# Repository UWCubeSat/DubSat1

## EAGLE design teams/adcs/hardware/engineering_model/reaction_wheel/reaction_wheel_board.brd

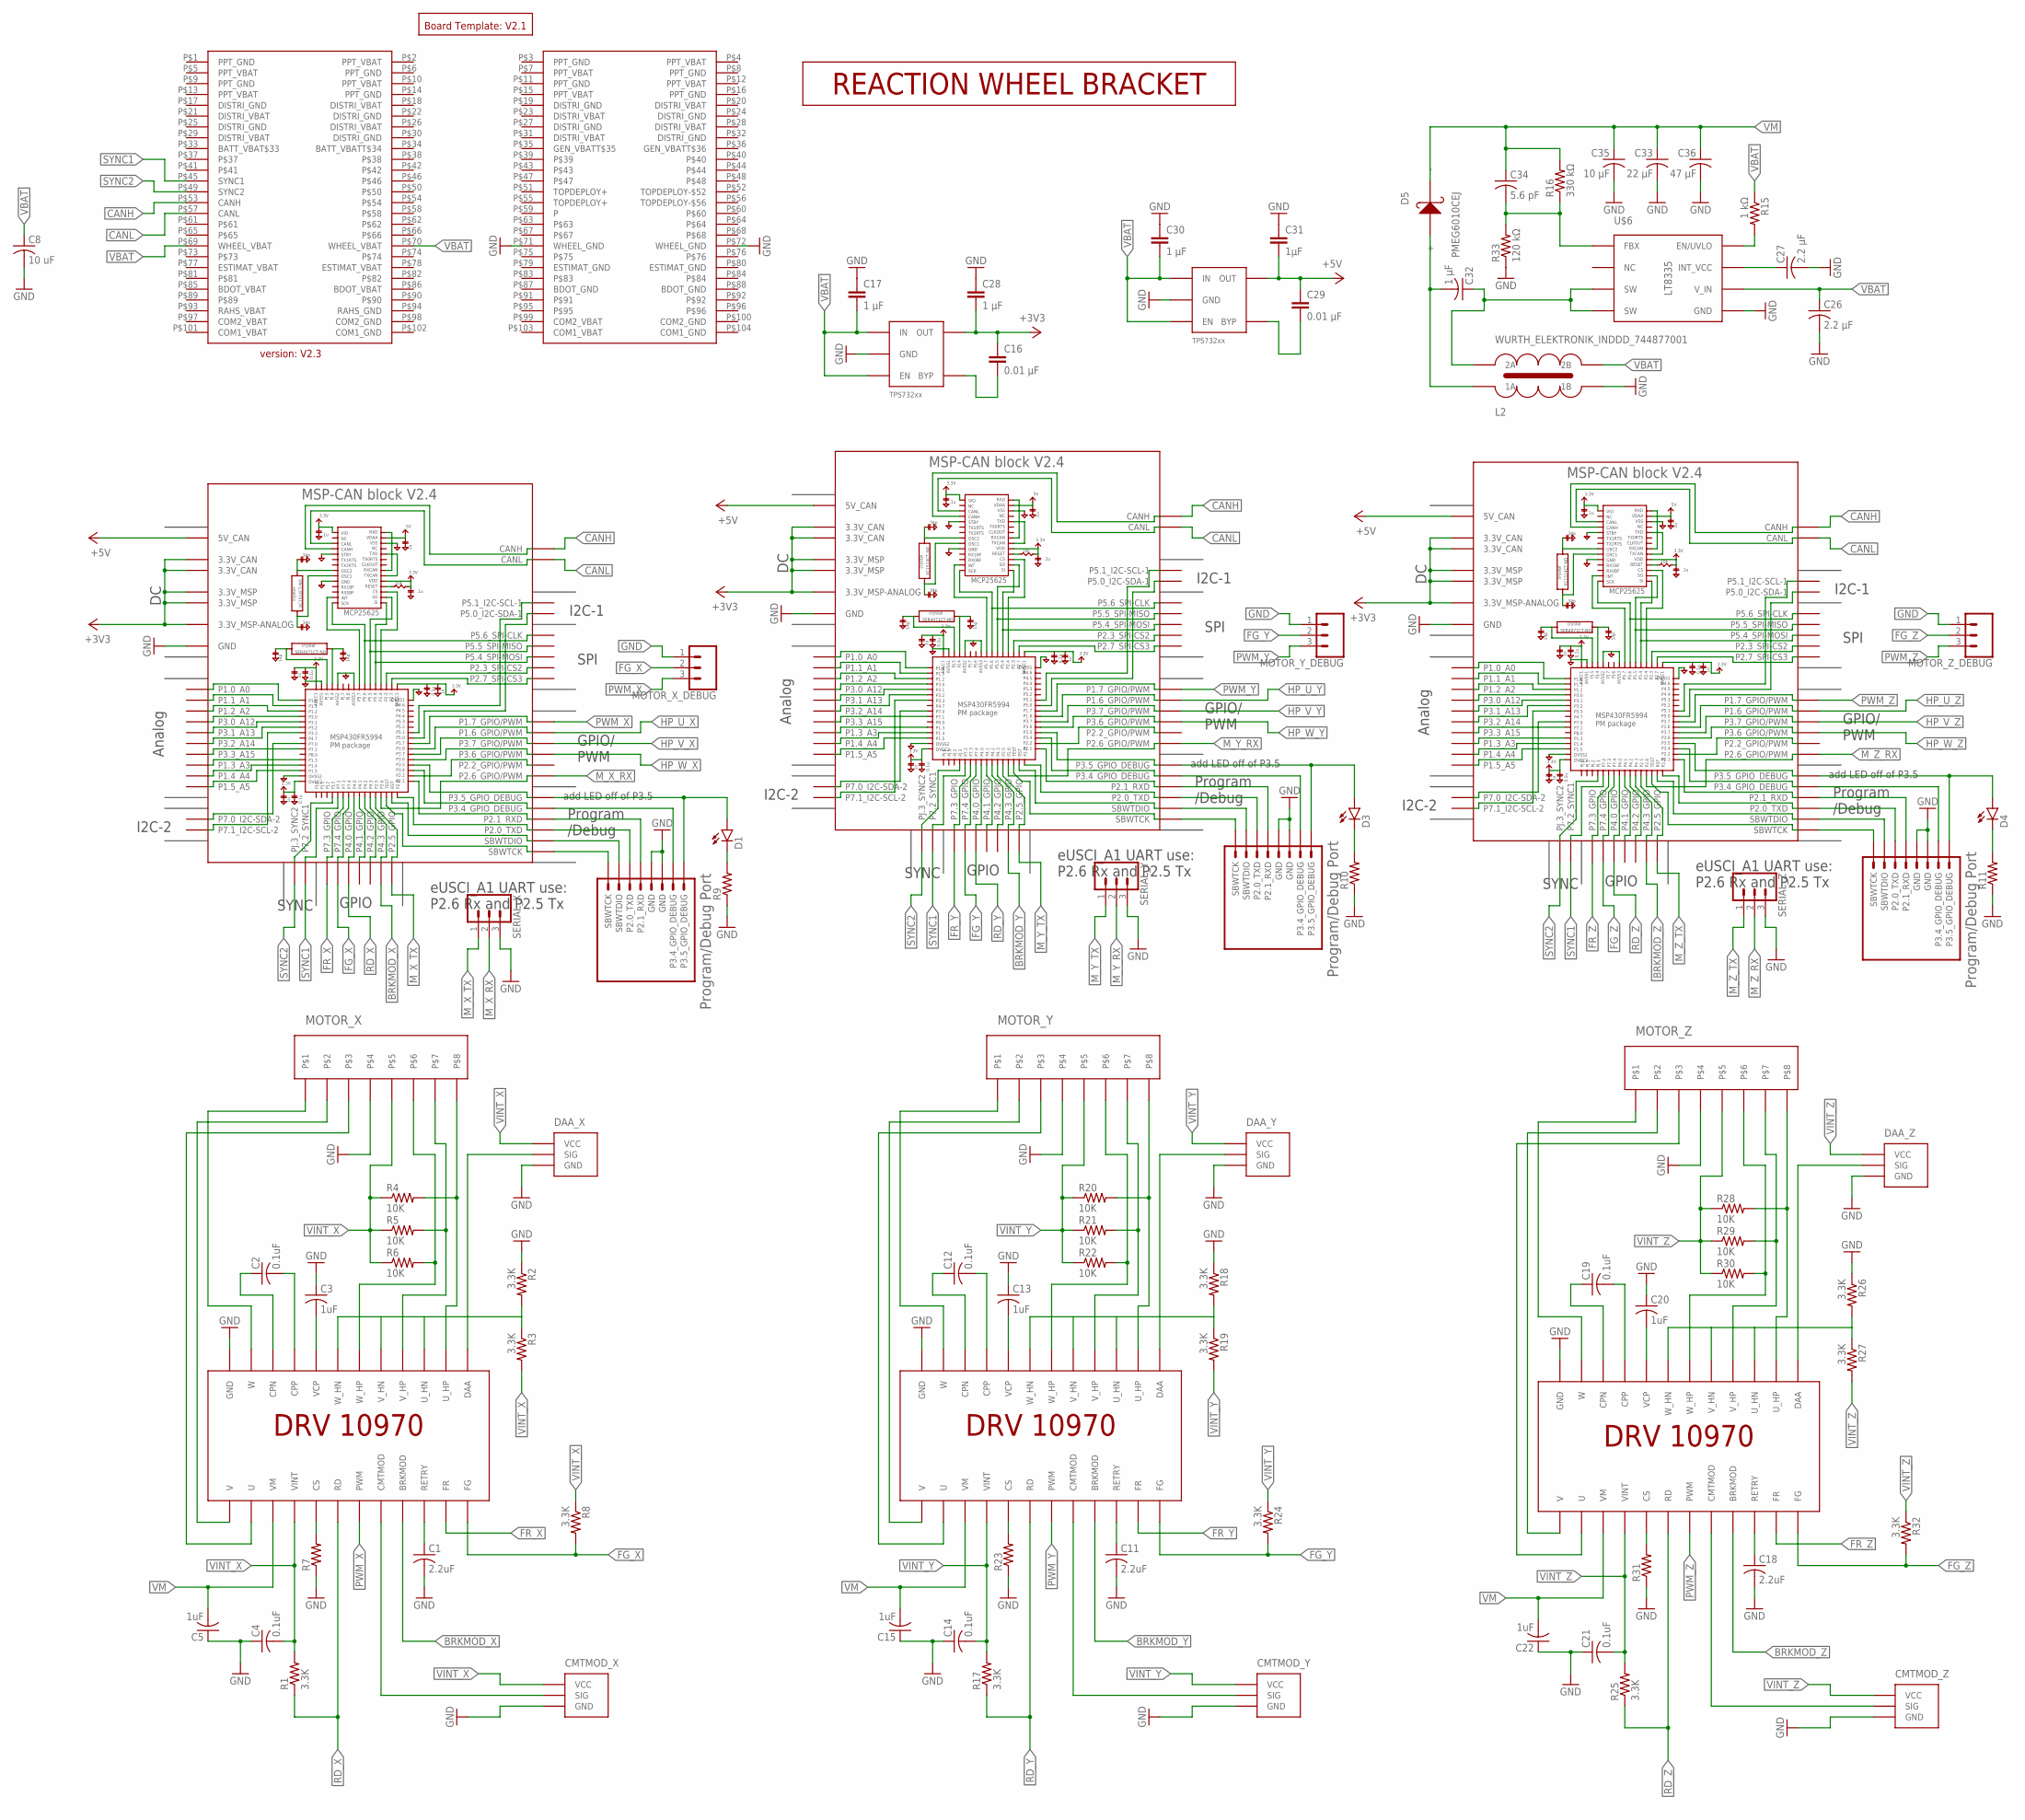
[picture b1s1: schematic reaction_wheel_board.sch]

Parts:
C1, C11, C18: 2.2uF; C1206
C2, C4, C12, C14, C19, C21: 0.1uF; C0805
C3, C5, C13, C15, C20, C22: 1uF; C1206
C8: 10 uF; C0805
C16, C29: 0.01 μF; 0805
C17, C28, C30: 1 μF; 0805
C26, C27: 2.2 μF; C0805
C31: 1μF; 0805
C32: 1 μF; C0805
C33: 22 μF; C1206
C34: 5.6 pF; C0805
C35: 10 μF; C0805
C36: 47 μF; C1206
CMTMOD_X: 0_OHM_JUMPER
CMTMOD_Y: 0_OHM_JUMPER
CMTMOD_Z: 0_OHM_JUMPER
D1, D3, D4: LED; LED-1206
D5: PMEG6010CEJ; SC-90
DAA_X: 0_OHM_JUMPER
DAA_Y: 0_OHM_JUMPER
DAA_Z: 0_OHM_JUMPER
L2: WURTH_ELEKTRONIK_INDDD_744877001
MOTOR_X: PICOLOCK_8
MOTOR_X_DEBUG: CONN_03LOCK; 1X03_LOCK
MOTOR_Y: PICOLOCK_8
MOTOR_Y_DEBUG: CONN_03LOCK; 1X03_LOCK
MOTOR_Z: PICOLOCK_8
MOTOR_Z_DEBUG: CONN_03LOCK; 1X03_LOCK
MSP_X_DEBUG: PROGRAM/DEBUG_PORT; 1X08_CONNECTOR
MSP_Y_DEBUG: PROGRAM/DEBUG_PORT; 1X08_CONNECTOR
MSP_Z_DEBUG: PROGRAM/DEBUG_PORT; 1X08_CONNECTOR
PC104: PC104_CONNECTOR
R1, R2, R3, R8, R17, R18, R19, R24, R25, R26, R27, R32: 3.3K; 0805
R4, R5, R6, R20, R21, R22, R28, R29, R30: 10K; 0805
R7, R9, R10, R11, R23, R31: RESISTOR0805; 0805
R15: 1 kΩ; 0805
R16: 330 kΩ; 0805
R33: 120 kΩ; 0805
SERIAL_X: CONN_03LOCK; 1X03_LOCK
SERIAL_Y: CONN_03LOCK; 1X03_LOCK
SERIAL_Z: CONN_03LOCK; 1X03_LOCK
U2, U3: TPS732XX; SOT-23-5
U$1: BOARD_TEMPLATESERCURED; BOARD_TEMPLATE_SECURED
U$3, U$10, U$13: MSP-CAN_BLOCK
U$6: LT8335; DDB
U$7, U$12, U$15: DRV10970
U$9: REACTION_WHEEL_BRACKET

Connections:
+3V3: C16.1, C28.2, U2.P$5 (OUT), U$3.3.3V@CAN1 (3.3V_CAN), U$3.3.3V@CAN2 (3.3V_CAN), U$3.3.3V@MSP1 (3.3V_MSP), U$3.3.3V@MSP2 (3.3V_MSP), U$3.3.3V_ANALOG@MSP2 (3.3V_MSP-ANALOG), U$10.3.3V@CAN1 (3.3V_CAN), U$10.3.3V@CAN2 (3.3V_CAN), U$10.3.3V@MSP1 (3.3V_MSP), U$10.3.3V@MSP2 (3.3V_MSP), U$10.3.3V_ANALOG@MSP2 (3.3V_MSP-ANALOG), U$13.3.3V@CAN1 (3.3V_CAN), U$13.3.3V@CAN2 (3.3V_CAN), U$13.3.3V@MSP1 (3.3V_MSP), U$13.3.3V@MSP2 (3.3V_MSP), U$13.3.3V_ANALOG@MSP2 (3.3V_MSP-ANALOG)
+5V: C29.1, C31.2, U3.P$5 (OUT), U$3.5V (5V_CAN), U$10.5V (5V_CAN), U$13.5V (5V_CAN)
BRKMOD_X: U$3.P4.3_GPIO, U$7.BRKMOD
BRKMOD_Y: U$10.P4.3_GPIO, U$12.BRKMOD
BRKMOD_Z: U$13.P4.3_GPIO, U$15.BRKMOD
CANH: PC104.P$53 (CANH), U$3.CANH, U$10.CANH, U$13.CANH
CANL: PC104.P$57 (CANL), U$3.CANL, U$10.CANL, U$13.CANL
CMTMOD_X: CMTMOD_X.P$2 (SIG), U$7.CMTMOD
CMTMOD_Y: CMTMOD_Y.P$2 (SIG), U$12.CMTMOD
CMTMOD_Z: CMTMOD_Z.P$2 (SIG), U$15.CMTMOD
CPN_X: C2.1, U$7.CPN
CPN_Y: C12.1, U$12.CPN
CPN_Z: C19.1, U$15.CPN
CPP_X: C2.2, U$7.CPP
CPP_Y: C12.2, U$12.CPP
CPP_Z: C19.2, U$15.CPP
CS_X: R7.2, U$7.CS
CS_Y: R23.2, U$12.CS
CS_Z: R31.2, U$15.CS
DAA_X: DAA_X.P$2 (SIG), U$7.DAA
DAA_Y: DAA_Y.P$2 (SIG), U$12.DAA
DAA_Z: DAA_Z.P$2 (SIG), U$15.DAA
EN_UVLO: R15.2, U$6.P$8 (EN/UVLO)
FBX: C34.2, R16.1, R33.2, U$6.P$1 (FBX)
FG_X: MOTOR_X_DEBUG.2, R8.2, U$3.P7.4_GPIO, U$7.FG
FG_Y: MOTOR_Y_DEBUG.2, R24.2, U$10.P7.4_GPIO, U$12.FG
FG_Z: MOTOR_Z_DEBUG.2, R32.2, U$13.P7.4_GPIO, U$15.FG
FR_X: U$3.P7.3_GPIO, U$7.FR
FR_Y: U$10.P7.3_GPIO, U$12.FR
FR_Z: U$13.P7.3_GPIO, U$15.FR
GND: C1.2, C3.1, C4.1, C5.1, C8.2, C11.2, C13.1, C14.1, C15.1, C17.1, C18.2, C20.1, C21.1, C22.1, C26.2, C27.2, C28.1, C30.1, C31.1, C33.2, C35.2, C36.2, CMTMOD_X.P$1 (GND), CMTMOD_Y.P$1 (GND), CMTMOD_Z.P$1 (GND), DAA_X.P$1 (GND), DAA_Y.P$1 (GND), DAA_Z.P$1 (GND), L2.P$2 (1B), MOTOR_X.P$4, MOTOR_X_DEBUG.1, MOTOR_Y.P$4, MOTOR_Y_DEBUG.1, MOTOR_Z.P$4, MOTOR_Z_DEBUG.1, MSP_X_DEBUG.5 (GND), MSP_X_DEBUG.6 (GND), MSP_Y_DEBUG.5 (GND), MSP_Y_DEBUG.6 (GND), MSP_Z_DEBUG.5 (GND), MSP_Z_DEBUG.6 (GND), PC104.P$71 (WHEEL_GND), PC104.P$72 (WHEEL_GND), R2.1, R7.1, R9.1, R10.1, R11.1, R18.1, R23.1, R26.1, R31.1, R33.1, SERIAL_X.3, SERIAL_Y.3, SERIAL_Z.3, U2.P$2 (GND), U3.P$2 (GND), U$3.GND@1 (GND), U$3.GND@2 (GND), U$3.GND@3 (GND), U$3.GND@4 (GND), U$3.GND@5 (GND), U$3.GND@7 (GND), U$3.GND@8 (GND), U$3.GND@9 (GND), U$3.GND@10 (GND), U$3.GND@11 (GND), U$3.GND@12 (GND), U$3.GND@13 (GND), U$3.GND@14 (GND), U$3.GND@15 (GND), U$3.GND@16 (GND), U$3.GND@17 (GND), U$3.GND@26 (GND), U$6.GND, U$6.P$5 (GND), U$7.GND@1 (GND), U$7.GND@2 (GND), U$10.GND@1 (GND), U$10.GND@2 (GND), U$10.GND@3 (GND), U$10.GND@4 (GND), U$10.GND@5 (GND), U$10.GND@7 (GND), U$10.GND@8 (GND), U$10.GND@9 (GND), U$10.GND@10 (GND), U$10.GND@11 (GND), U$10.GND@12 (GND), U$10.GND@13 (GND), U$10.GND@14 (GND), U$10.GND@15 (GND), U$10.GND@16 (GND), U$10.GND@17 (GND), U$10.GND@26 (GND), U$12.GND@1 (GND), U$12.GND@2 (GND), U$13.GND@1 (GND), U$13.GND@2 (GND), U$13.GND@3 (GND), U$13.GND@4 (GND), U$13.GND@5 (GND), U$13.GND@7 (GND), U$13.GND@8 (GND), U$13.GND@9 (GND), U$13.GND@10 (GND), U$13.GND@11 (GND), U$13.GND@12 (GND), U$13.GND@13 (GND), U$13.GND@14 (GND), U$13.GND@15 (GND), U$13.GND@16 (GND), U$13.GND@17 (GND), U$13.GND@26 (GND), U$15.GND@1 (GND), U$15.GND@2 (GND)
GPIO_DEBUG_3.4_X: MSP_X_DEBUG.7 (P3.4_GPIO_DEBUG), U$3.P3.4_GPIO_DEBUG
GPIO_DEBUG_3.4_Y: MSP_Y_DEBUG.7 (P3.4_GPIO_DEBUG), U$10.P3.4_GPIO_DEBUG
GPIO_DEBUG_3.4_Z: MSP_Z_DEBUG.7 (P3.4_GPIO_DEBUG), U$13.P3.4_GPIO_DEBUG
GPIO_DEBUG_3.5_X: D1.A, MSP_X_DEBUG.8 (P3.5_GPIO_DEBUG), U$3.P3.5_GPIO_DEBUG
GPIO_DEBUG_3.5_Y: D3.A, MSP_Y_DEBUG.8 (P3.5_GPIO_DEBUG), U$10.P3.5_GPIO_DEBUG
GPIO_DEBUG_3.5_Z: D4.A, MSP_Z_DEBUG.8 (P3.5_GPIO_DEBUG), U$13.P3.5_GPIO_DEBUG
HN_X: R2.2, R3.1, U$7.U_HN, U$7.V_HN, U$7.W_HN
HN_Y: R18.2, R19.1, U$12.U_HN, U$12.V_HN, U$12.W_HN
HN_Z: R26.2, R27.1, U$15.U_HN, U$15.V_HN, U$15.W_HN
HP_U_X: MOTOR_X.P$8, R4.2, U$3.P1.6_GPIO/PWM, U$7.U_HP
HP_U_Y: MOTOR_Y.P$8, R20.2, U$10.P1.6_GPIO/PWM, U$12.U_HP
HP_U_Z: MOTOR_Z.P$8, R28.2, U$13.P1.6_GPIO/PWM, U$15.U_HP
HP_V_X: MOTOR_X.P$7, R5.2, U$3.P3.7_GPIO/PWM, U$7.V_HP
HP_V_Y: MOTOR_Y.P$7, R21.2, U$10.P3.7_GPIO/PWM, U$12.V_HP
HP_V_Z: MOTOR_Z.P$7, R29.2, U$13.P3.7_GPIO/PWM, U$15.V_HP
HP_W_X: MOTOR_X.P$6, R6.2, U$3.P3.6_GPIO/PWM, U$7.W_HP
HP_W_Y: MOTOR_Y.P$6, R22.2, U$10.P3.6_GPIO/PWM, U$12.W_HP
HP_W_Z: MOTOR_Z.P$6, R30.2, U$13.P3.6_GPIO/PWM, U$15.W_HP
INT_VCC: C27.1, U$6.P$7 (INT_VCC)
LDO_3V3_BYP2: C16.2, U2.P$4 (BYP)
LDO_5V_BYP: C29.2, U3.P$4 (BYP)
M_X_RX: SERIAL_X.2, U$3.P2.6_GPIO/PWM
M_X_TX: SERIAL_X.1, U$3.P2.5_GPIO
M_Y_RX: SERIAL_Y.2, U$10.P2.6_GPIO/PWM
M_Y_TX: SERIAL_Y.1, U$10.P2.5_GPIO
M_Z_RX: SERIAL_Z.2, U$13.P2.6_GPIO/PWM
M_Z_TX: SERIAL_Z.1, U$13.P2.5_GPIO
unnamed: D4.C, R11.2
unnamed: D3.C, R10.2
unnamed: D1.C, R9.2
PWM_X: MOTOR_X_DEBUG.3, U$3.P1.7_GPIO/PWM, U$7.PWM
PWM_Y: MOTOR_Y_DEBUG.3, U$10.P1.7_GPIO/PWM, U$12.PWM
PWM_Z: MOTOR_Z_DEBUG.3, U$13.P1.7_GPIO/PWM, U$15.PWM
RD_X: R1.1, U$3.P4.0_GPIO, U$7.RD
RD_Y: R17.1, U$10.P4.0_GPIO, U$12.RD
RD_Z: R25.1, U$13.P4.0_GPIO, U$15.RD
RETRY_X: C1.1, U$7.RETRY
RETRY_Y: C11.1, U$12.RETRY
RETRY_Z: C18.1, U$15.RETRY
RXD_X: MSP_X_DEBUG.4 (P2.1_RXD), U$3.P2.1_RXD
RXD_Y: MSP_Y_DEBUG.4 (P2.1_RXD), U$10.P2.1_RXD
RXD_Z: MSP_Z_DEBUG.4 (P2.1_RXD), U$13.P2.1_RXD
SBWTCK_X: MSP_X_DEBUG.SBWTCK, U$3.SBWTCK
SBWTCK_Y: MSP_Y_DEBUG.SBWTCK, U$10.SBWTCK
SBWTCK_Z: MSP_Z_DEBUG.SBWTCK, U$13.SBWTCK
SBWTDIO_X: MSP_X_DEBUG.2 (SBWTDIO), U$3.SBWTDIO
SBWTDIO_Y: MSP_Y_DEBUG.2 (SBWTDIO), U$10.SBWTDIO
SBWTDIO_Z: MSP_Z_DEBUG.2 (SBWTDIO), U$13.SBWTDIO
SW: C32.1, L2.P$3 (2A), U$6.P$3 (SW), U$6.P$4 (SW)
SYNC1: PC104.P$45 (SYNC1), U$3.P7.2_SYNC1, U$10.P7.2_SYNC1, U$13.P7.2_SYNC1
SYNC2: PC104.P$49 (SYNC2), U$3.PJ.3_SYNC2, U$10.PJ.3_SYNC2, U$13.PJ.3_SYNC2
TXD_X: MSP_X_DEBUG.3 (P2.0_TXD), U$3.P2.0_TXD
TXD_Y: MSP_Y_DEBUG.3 (P2.0_TXD), U$10.P2.0_TXD
TXD_Z: MSP_Z_DEBUG.3 (P2.0_TXD), U$13.P2.0_TXD
U_X: MOTOR_X.P$3, U$7.U
U_Y: MOTOR_Y.P$3, U$12.U
U_Z: MOTOR_Z.P$3, U$15.U
VBAT: C8.1, C17.2, C26.1, C30.2, L2.P$4 (2B), PC104.P$69 (WHEEL_VBAT), PC104.P$70 (WHEEL_VBAT), R15.1, U2.P$1 (IN), U2.P$3 (EN), U3.P$1 (IN), U3.P$3 (EN), U$6.P$6 (V_IN)
VCP_X: C3.2, U$7.VCP
VCP_Y: C13.2, U$12.VCP
VCP_Z: C20.2, U$15.VCP
VD: C32.2, D5.P$1 (+), L2.P$1 (1A)
VINT_X: C4.2, CMTMOD_X.P$3 (VCC), DAA_X.P$3 (VCC), MOTOR_X.P$5, R1.2, R3.2, R4.1, R5.1, R6.1, R8.1, U$7.VINT
VINT_Y: C14.2, CMTMOD_Y.P$3 (VCC), DAA_Y.P$3 (VCC), MOTOR_Y.P$5, R17.2, R19.2, R20.1, R21.1, R22.1, R24.1, U$12.VINT
VINT_Z: C21.2, CMTMOD_Z.P$3 (VCC), DAA_Z.P$3 (VCC), MOTOR_Z.P$5, R25.2, R27.2, R28.1, R29.1, R30.1, R32.1, U$15.VINT
VM: C5.2, C15.2, C22.2, C33.1, C34.1, C35.1, C36.1, D5.P$2 (-), R16.2, U$7.VM, U$12.VM, U$15.VM
V_X: MOTOR_X.P$2, U$7.V
V_Y: MOTOR_Y.P$2, U$12.V
V_Z: MOTOR_Z.P$2, U$15.V
W_X: MOTOR_X.P$1, U$7.W
W_Y: MOTOR_Y.P$1, U$12.W
W_Z: MOTOR_Z.P$1, U$15.W

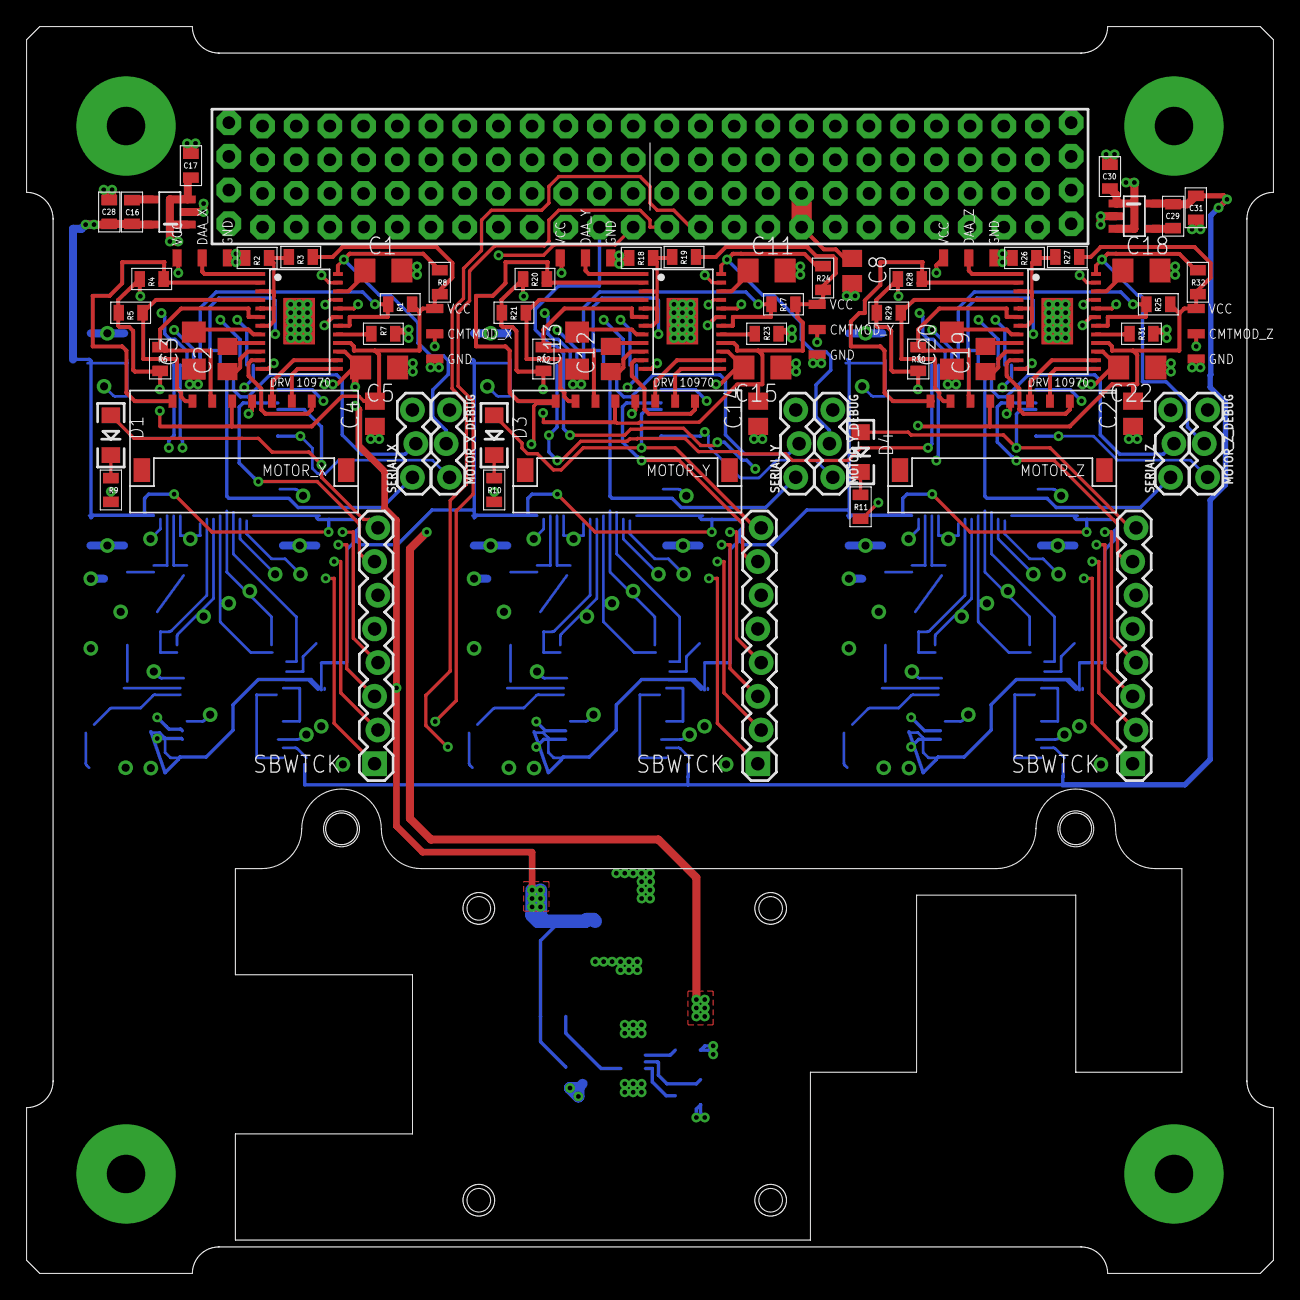
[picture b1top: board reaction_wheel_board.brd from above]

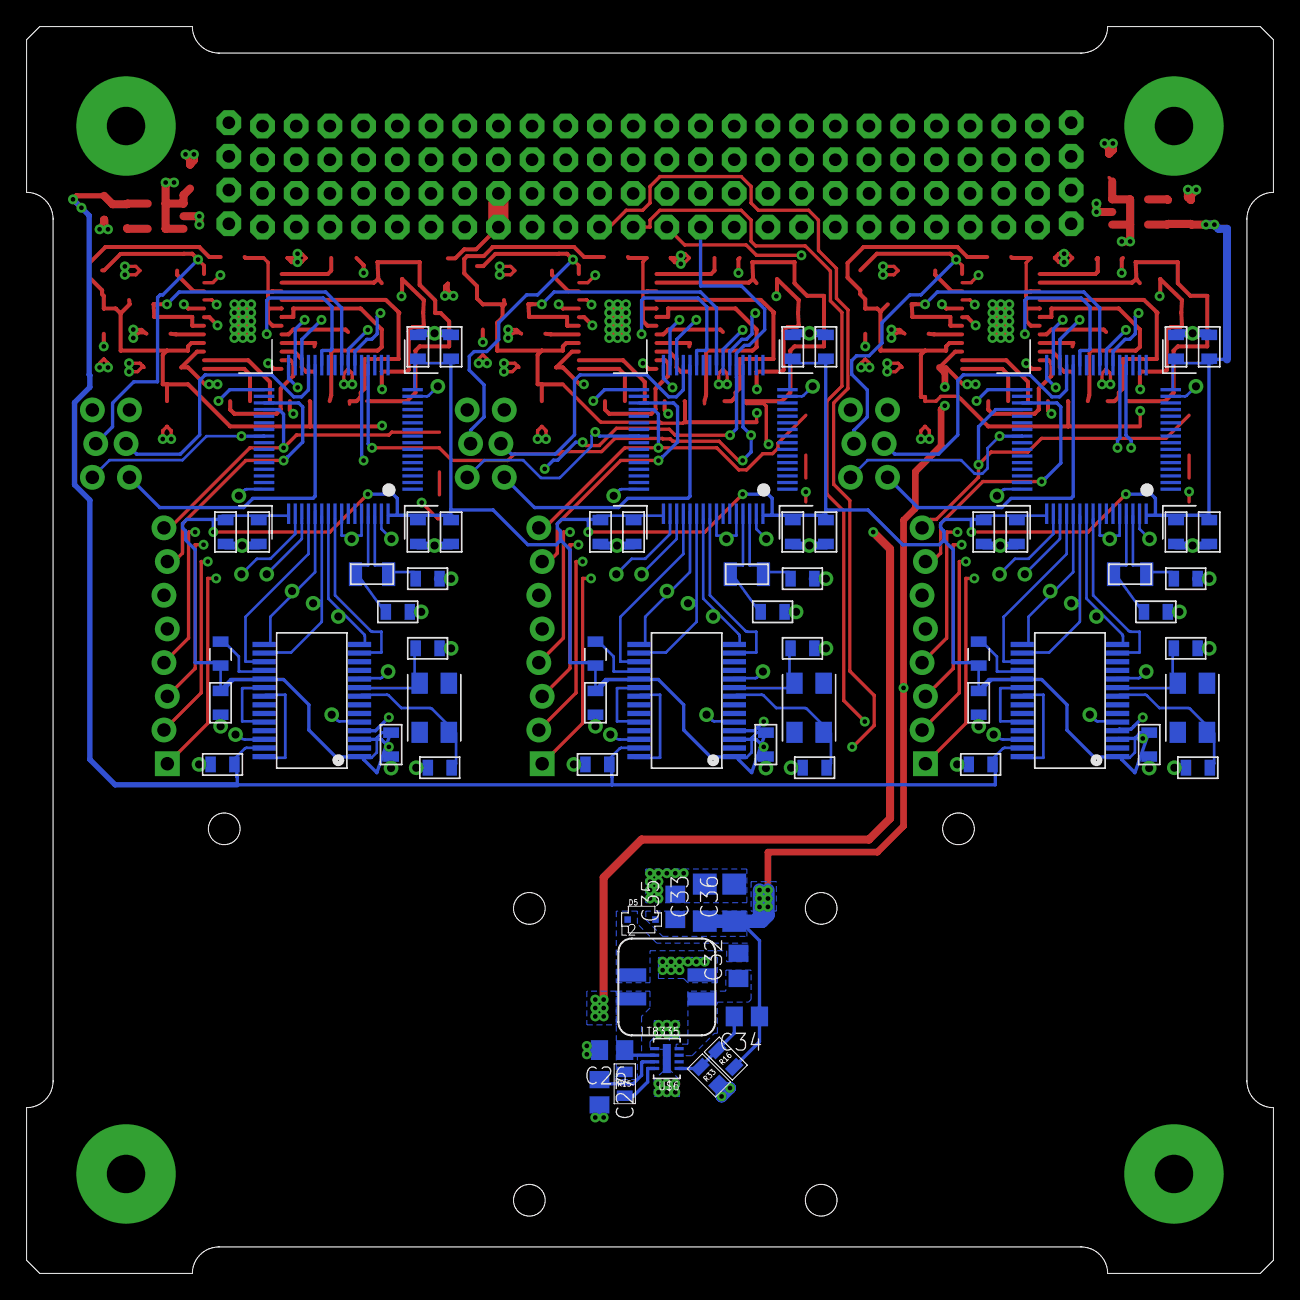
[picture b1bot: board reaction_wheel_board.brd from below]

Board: 4 copper layers, 94.0 x 94.0 mm, 94 parts (16 on the bottom side), 103 nets.

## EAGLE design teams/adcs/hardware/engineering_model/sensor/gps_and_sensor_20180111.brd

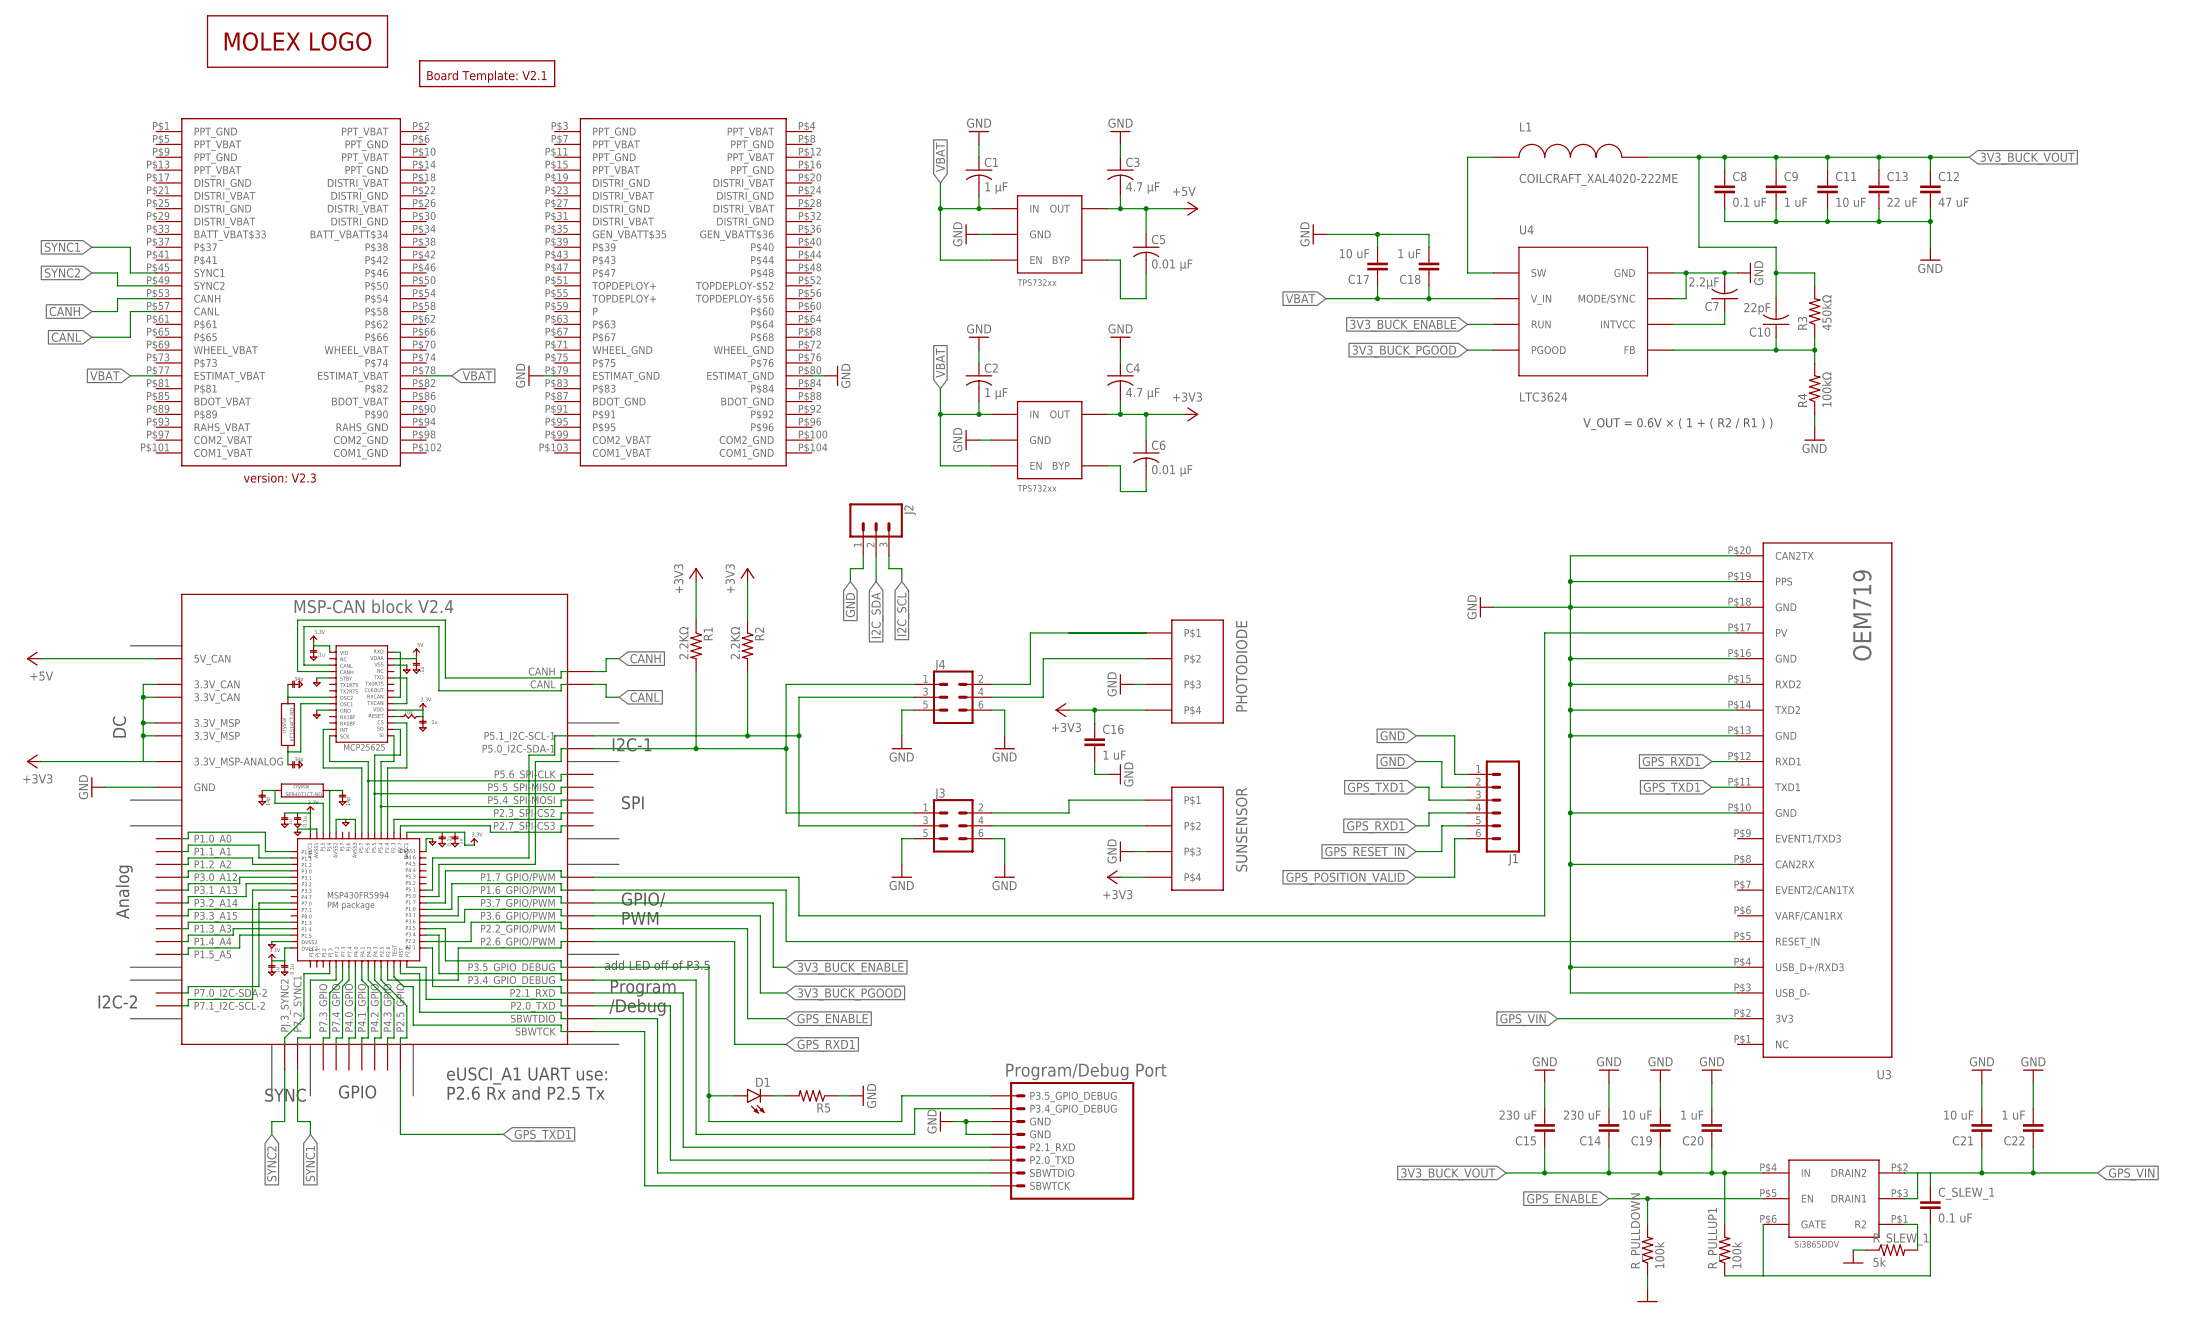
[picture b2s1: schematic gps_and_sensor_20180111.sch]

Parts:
B1: BOARD_TEMPLATE1; BOARD_TEMPLATE
BLK1: MSP-CAN_BLOCK
C1, C2: 1 μF; C0805
C3, C4: 4.7 μF; C0805
C5, C6: 0.01 μF; C0805
C7: 2.2μF; C0805
C8: 0.1 uF; 0805
C9, C16, C18, C20, C22: 1 uF; 0805
C10: 22pF; C0805
C11, C17, C19, C21: 10 uF; 0805
C12: 47 uF; 1206
C13: 22 uF; 1206
C14, C15: 230 uF; PANASONIC_SVPG
CONN1: PC104_CONNECTOR
C_SLEW_1: 0.1 uF; 0805
D1: LED; LED-1206
J1: CONN_06LOCK; 1X06_LOCK
J2: CONN_03LOCK; 1X03_LOCK
J3, J4: CONN_03X22X3_SILK_MALE_PTH; 2X3
L1: COILCRAFT_XAL4020-222ME; COILCRAFT_XAL4020
PHOTODIODE: PICOLOCK_4
R1, R2: 2.2KΩ; R0805
R3: 450kΩ; R0805
R4: 100kΩ; R0805
R5: RESISTOR0805; 0805
R_PULLDOWN: 100k; 0805
R_PULLUP1: 100k; 0805
R_SLEW_1: 5k; 0805
SUNSENSOR: PICOLOCK_4
U1, U2: TPS732XX; SOT-23-5
U3: OEM719
U4: LTC3624
U$1: LOGO_MOLEX
U$2: PROGRAM/DEBUG_PORT; 1X08_CONNECTOR
U$3: SI3865DDV; TSOP-6

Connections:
3V3_BUCK_ENABLE: BLK1.P3.7_GPIO/PWM, U4.RUN
3V3_BUCK_FB: C10.1, R3.1, R4.2, U4.FB
3V3_BUCK_INTVCC: C7.1, U4.INTVCC
3V3_BUCK_PGOOD: BLK1.P3.6_GPIO/PWM, U4.PGOOD
3V3_BUCK_SW: L1.P$1, U4.SW
3V3_BUCK_VOUT: C8.1, C9.1, C10.2, C11.1, C12.1, C13.1, C14.POS (1), C15.POS (1), C19.1, C20.1, L1.P$2, R3.2, R_PULLUP1.2, U$3.P$4 (IN)
CANH: BLK1.CANH, CONN1.P$53 (CANH)
CANL: BLK1.CANL, CONN1.P$57 (CANL)
GND: BLK1.GND@1 (GND), BLK1.GND@2 (GND), BLK1.GND@3 (GND), BLK1.GND@4 (GND), BLK1.GND@5 (GND), BLK1.GND@7 (GND), BLK1.GND@8 (GND), BLK1.GND@9 (GND), BLK1.GND@10 (GND), BLK1.GND@11 (GND), BLK1.GND@12 (GND), BLK1.GND@13 (GND), BLK1.GND@14 (GND), BLK1.GND@15 (GND), BLK1.GND@16 (GND), BLK1.GND@17 (GND), BLK1.GND@26 (GND), C1.1, C2.1, C3.1, C4.1, C7.2, C8.2, C9.2, C11.2, C12.2, C13.2, C14.NEG (2), C15.NEG (2), C16.2, C17.2, C18.2, C19.2, C20.2, C21.2, C22.2, CONN1.P$79 (ESTIMAT_GND), CONN1.P$80 (ESTIMAT_GND), J1.1, J1.2, J2.1, J3.5, J3.6, J4.5, J4.6, PHOTODIODE.P$3, R4.1, R5.1, R_PULLDOWN.1, R_SLEW_1.1, SUNSENSOR.P$3, U1.P$2 (GND), U2.P$2 (GND), U3.P$3 (USB_D-), U3.P$4 (USB_D+/RXD3), U3.P$8 (CAN2RX), U3.P$10 (GND), U3.P$13 (GND), U3.P$14 (TXD2), U3.P$15 (RXD2), U3.P$16 (GND), U3.P$18 (GND), U3.P$19 (PPS), U3.P$20 (CAN2TX), U4.GND@1 (GND), U4.GND@PAD (GND), U4.MODE/SYNC, U$2.5 (GND), U$2.6 (GND)
GPS_ENABLE: BLK1.P2.2_GPIO/PWM, R_PULLDOWN.2, U$3.P$5 (EN)
GPS_POSITION_VALID: BLK1.P1.7_GPIO/PWM, J1.6, U3.P$17 (PV)
GPS_RESET_IN: BLK1.P1.6_GPIO/PWM, J1.5, U3.P$5 (RESET_IN)
GPS_RXD1: BLK1.P2.6_GPIO/PWM, J1.4, U3.P$12 (RXD1)
GPS_TXD1: BLK1.P2.5_GPIO, J1.3, U3.P$11 (TXD1)
GPS_VIN: C21.1, C22.1, C_SLEW_1.1, U3.P$2 (3V3), U$3.P$2 (DRAIN2), U$3.P$3 (DRAIN1)
I2C_SCL: BLK1.P5.1_I2C-SCL-1, J2.3, J3.3, J4.3, R2.2
I2C_SDA: BLK1.P5.0_I2C-SDA-1, J2.2, J3.1, J4.1, R1.2
LDO_3V3: BLK1.3.3V@CAN1 (3.3V_CAN), BLK1.3.3V@CAN2 (3.3V_CAN), BLK1.3.3V@MSP1 (3.3V_MSP), BLK1.3.3V@MSP2 (3.3V_MSP), BLK1.3.3V_ANALOG@MSP2 (3.3V_MSP-ANALOG), C4.2, C6.1, C16.1, PHOTODIODE.P$4, R1.1, R2.1, SUNSENSOR.P$4, U2.P$5 (OUT)
LDO_3V3_BYP: C6.2, U2.P$4 (BYP)
LDO_5V: BLK1.5V (5V_CAN), C3.2, C5.1, U1.P$5 (OUT)
LDO_5V_BYP: C5.2, U1.P$4 (BYP)
unnamed: BLK1.P3.5_GPIO_DEBUG, D1.A, U$2.8 (P3.5_GPIO_DEBUG)
unnamed: R_SLEW_1.2, U$3.P$1 (R2)
unnamed: BLK1.P3.4_GPIO_DEBUG, U$2.7 (P3.4_GPIO_DEBUG)
unnamed: C_SLEW_1.2, R_PULLUP1.1, U$3.P$6 (GATE)
unnamed: BLK1.P2.1_RXD, U$2.4 (P2.1_RXD)
unnamed: BLK1.P2.0_TXD, U$2.3 (P2.0_TXD)
unnamed: BLK1.SBWTDIO, U$2.2 (SBWTDIO)
unnamed: BLK1.SBWTCK, U$2.SBWTCK
unnamed: D1.C, R5.2
PHOTODIODE_SCL: J4.4, PHOTODIODE.P$2
PHOTODIODE_SDA: J4.2, PHOTODIODE.P$1
SUNSENSOR_SCL: J3.4, SUNSENSOR.P$2
SUNSENSOR_SDA: J3.2, SUNSENSOR.P$1
SYNC1: BLK1.P7.2_SYNC1, CONN1.P$45 (SYNC1)
SYNC2: BLK1.PJ.3_SYNC2, CONN1.P$49 (SYNC2)
VBAT: C1.2, C2.2, C17.1, C18.1, CONN1.P$77 (ESTIMAT_VBAT), CONN1.P$78 (ESTIMAT_VBAT), U1.P$1 (IN), U1.P$3 (EN), U2.P$1 (IN), U2.P$3 (EN), U4.V_IN

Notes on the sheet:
V_OUT = 0.6V × ( 1 + ( R2 / R1 ) )

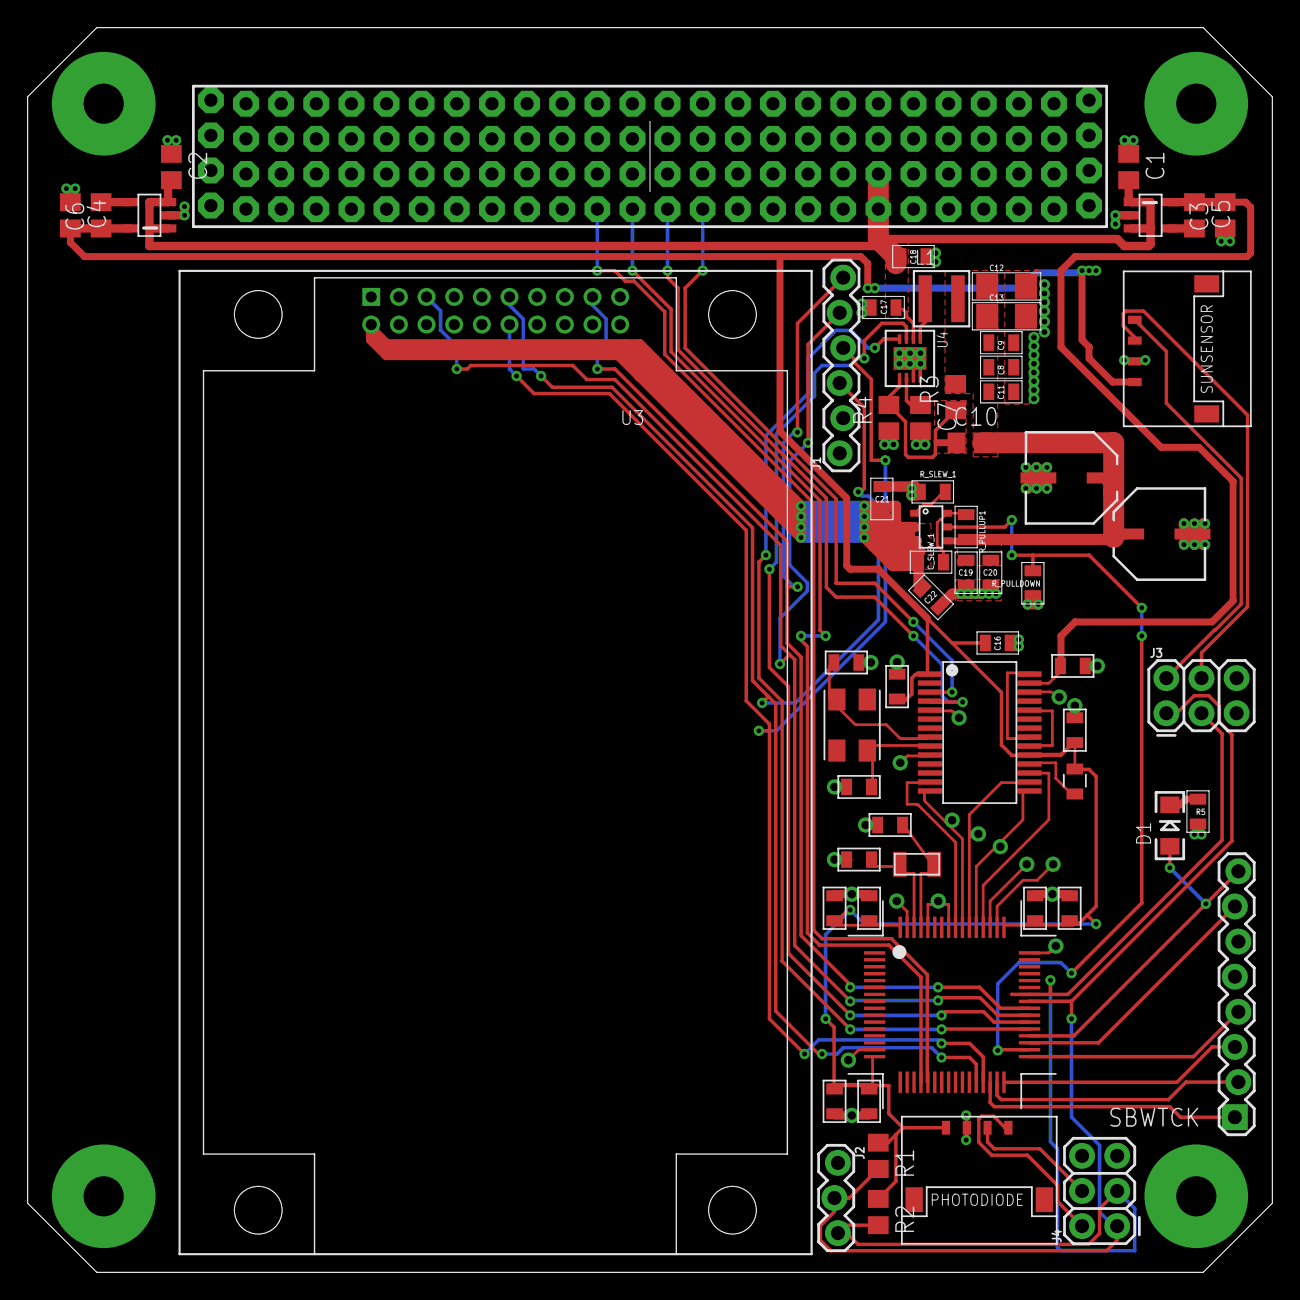
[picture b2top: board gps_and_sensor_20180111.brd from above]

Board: 2 copper layers, 90.0 x 90.0 mm, 49 parts (1 on the bottom side), 37 nets.

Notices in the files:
parts and their libraries:
SparkFun-Connectors: Licensing: Creative Commons ShareAlike 4.0 International - https://creativecommons.org/licenses/by-sa/4.0
